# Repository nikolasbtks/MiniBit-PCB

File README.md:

# MiniBit-PCB

## Description

This project demonstrates a custom 2-layer PCB containing the ESP32-S3-Mini microcontroller. This board can be used for embedded development or IoT applications using multiple peripherals.

## Components

1. Microcontroller: ESP32-S3-Mini
   - 512 KB SRAM and 8 MB Flash
   - 240 MHz clock speed 
   
2. USB Connectivity:
   - USB Type-C for data and power 
   - USBLC6-2SC6 for ESD protection

3. Power Supply: AP2112K-3.3 
   - Voltage regulator for stable 3.3V output
  
4. Headers:
   - JTAG headers for debugging
   - GPIO, I2C, UART headers for external connections

## Disclaimer

This project is currently in **testing phase**. The provided documentation is shared for prototyping and learning purposes. If you choose to manufacture and use the board, please proceed with care, as it has not yet been fully validated.

## Schematic and PCB Design

The board was designed using KiCad. Files from the PCB design can be found in the **hardware** folder for board manufacture. This folder includes:

- PCB Schematic 
- PCB Layout
- Gerber files
- Assembly files

## How to Use

1. Power the board
   - Use a USB Type-C cable to power the board.
   
2. Microcontroller Programming:
   - Use Arduino IDE or any other platform to program the microcontroller.
   - Use a debugger with JTAG headers.

3. Peripheral Access
   - Use the GPIO, I2C and UART headers to connect peripherals.

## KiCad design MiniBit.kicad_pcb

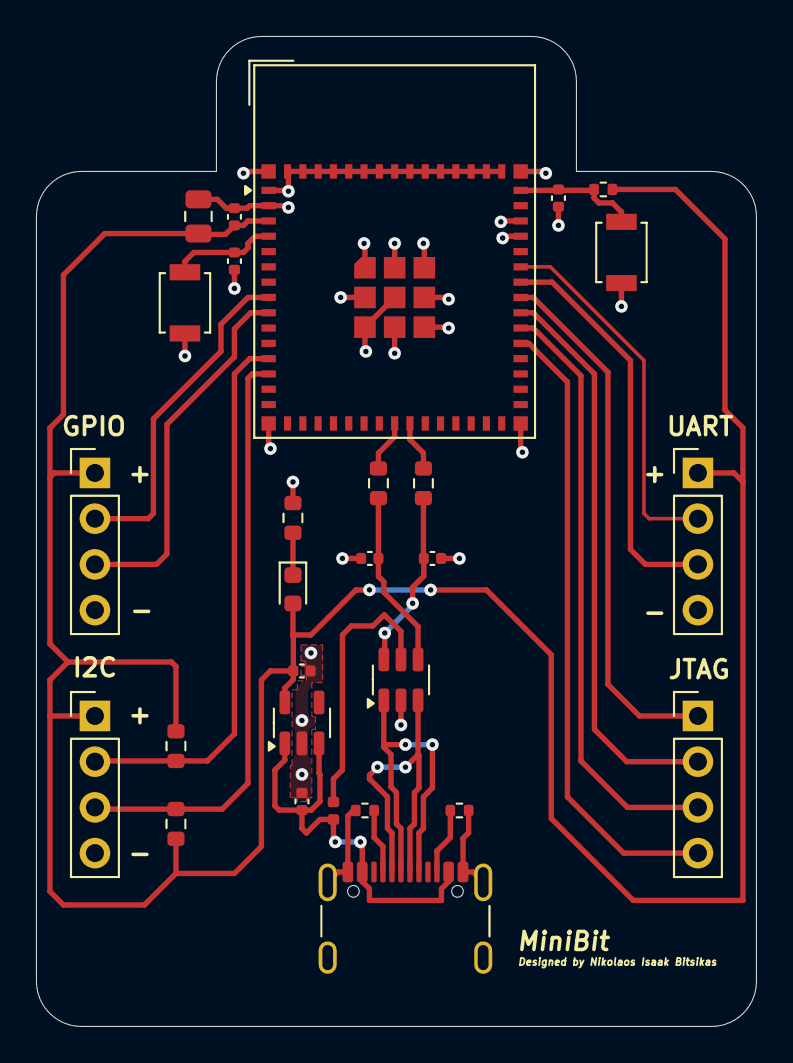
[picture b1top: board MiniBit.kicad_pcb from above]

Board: 2 copper layers, 40.0 x 55.0 mm, 28 parts (0 on the bottom side), 25 nets.

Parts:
C1, C3, C4: 0.1μF; C_0402_1005Metric
C2: 22μF; C_0805_2012Metric
C5, C6: 1μF; C_0402_1005Metric
C7, C8: 10nF; C_0402_1005Metric
D1: Red LED; LED_0603_1608Metric
F1: 500mA; Fuse_0402_1005Metric
J1, J2, J3, J4: Conn_01x04_Pin; PinHeader_1x04_P2.54mm_Vertical
J5: USB_C_Receptacle_USB2.0_16P; USB_C_Receptacle_GCT_USB4105-xx-A_16P_TopMnt_Horizontal
R1: 10k; R_0402_1005Metric
R2: 100R; R_0603_1608Metric
R3, R4: 5.1k; R_0402_1005Metric
R5, R6: 22R; R_0603_1608Metric
R7, R8: 1k5; R_0603_1608Metric
SW1, SW2: SW_SPST; SW_SPST_B3U-1000P
U1: ESP32-S3-MINI-1; ESP32-S2-MINI-1
U2: USBLC6-2SC6; SOT-23-6
U3: AP2112K-3.3; SOT-23-5

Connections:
+3.3V: C1.1, C2.1, C6.1, D1.2 (A), J1.1, J2.1, J4.1, R1.1, R7.1, R8.1, U1.3 (3V3), U3.5 (VOUT)
+5V: F1.2, U2.5 (VBUS)
/USB_N: R5.1, U1.23 (IO19)
/USB_P: R6.1, U1.24 (IO20)
BOOT: C4.1, SW2.2 (B), U1.4 (IO0)
D+: J5.A6 (D+), J5.B6 (D+), U2.1 (I/O1)
D-: J5.A7 (D-), J5.B7 (D-), U2.3 (I/O2)
GND: C1.2, C2.2, C3.2, C4.2, C5.2, C6.2, C7.2, C8.2, J1.4, J2.4, J4.4, J5.A1 (GND), J5.A12 (GND), J5.B1 (GND), J5.B12 (GND), J5.S1 (SHIELD), R2.2, R3.1, R4.1, SW1.1 (A), SW2.1 (A), U1.1 (GND), U1.2 (GND), U1.42 (GND), U1.43 (GND), U1.46 (GND), U1.47 (GND), U1.48 (GND), U1.49 (GND), U1.50 (GND), U1.51 (GND), U1.52 (GND), U1.53 (GND), U1.54 (GND), U1.55 (GND), U1.56 (GND), U1.57 (GND), U1.58 (GND), U1.59 (GND), U1.60 (GND), U1.61 (GND), U1.62 (GND), U1.63 (GND), U1.64 (GND), U1.65 (GND), U2.2 (GND), U3.2 (GND)
IO4: J4.2, U1.8 (IO4)
IO5: J4.3, U1.9 (IO5)
unnamed: D1.1 (K), R2.1
unnamed: J5.A5 (CC1), R3.2
unnamed: J5.B5 (CC2), R4.2
RESET: C3.1, R1.2, SW1.2 (B), U1.45 (EN)
RX: J2.2, U1.40 (RXD0)
SCL: J1.3, R8.2, U1.13 (IO9)
SDA: J1.2, R7.2, U1.12 (IO8)
TCK: J3.1, U1.38 (IO42)
TDI: J3.3, U1.36 (IO40)
TDO: J3.2, U1.37 (IO41)
TMS: J3.4, U1.35 (IO39)
TX: J2.3, U1.39 (TXD0)
USB_D+: C8.1, R6.2, U2.6 (I/O1)
USB_D-: C7.1, R5.2, U2.4 (I/O2)
VBUS: C5.1, F1.1, J5.A4 (VBUS), J5.A9 (VBUS), J5.B4 (VBUS), J5.B9 (VBUS), U3.1 (VIN), U3.3 (EN)
